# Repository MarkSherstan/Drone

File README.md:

# Drone
Mechanical, electrical, and software package for a custom quadcopter drone.

## Mechanical 
Designed using Fusion 360 and 3D printed on a Prusa MK3 printer. 

## Electrical
Custom PCBs designed in KiCad for the brain, power distribution, and signal indication. 
- Flight Controller
- Power Distribution Board 
- Lights 

## Software
C++ and custom libraries for controlling and stabilizing the UAV. Compiled with PlatformIO.

## Future Ideas
### Electrical
- Design ESCs
- 3.3 V flight controller (8 MHz suffcient?)
- Polyfuses on outputs
- PDB also ESC (active cooling?) - Have regulated outputs 
- PDB is part of frame (1 Oz copper)
- More powerful chip - RPi / STM32 / 2560 - Internet connection?

### Software 
- Test the crystal: How much time are we loosing? Try different caps.

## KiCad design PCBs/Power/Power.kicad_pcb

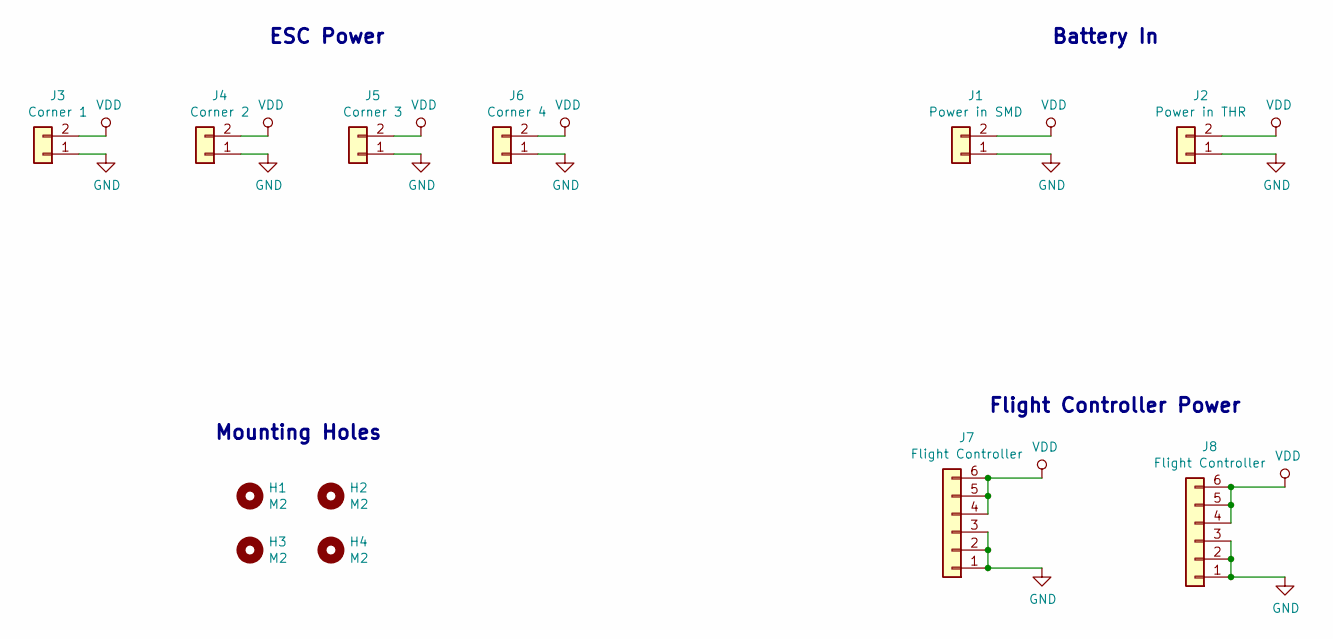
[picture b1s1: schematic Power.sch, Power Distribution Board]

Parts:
H1, H2, H3, H4: M2; MountingHole_2.2mm_M2_ISO14580_Pad
J1: Power in SMD; SMD-Power
J2: Power in THR; THR-Power
J3: Corner 1; Corner-Pad
J4: Corner 2; Corner-Pad
J5: Corner 3; Corner-Pad
J6: Corner 4; Corner-Pad
J7: Flight Controller; JST_GH_BM06B-GHS-TBT_1x06-1MP_P1.25mm_Vertical
J8: Flight Controller; JST_GH_SM06B-GHS-TB_1x06-1MP_P1.25mm_Horizontal

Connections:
GND: J1.1, J2.1, J3.1, J4.1, J5.1, J6.1, J7.1, J7.2, J7.3, J8.1, J8.2, J8.3
VDD: J1.2, J2.2, J3.2, J4.2, J5.2, J6.2, J7.4, J7.5, J7.6, J8.4, J8.5, J8.6

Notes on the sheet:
ESC Power
Battery In
Mounting Holes
Flight Controller Power

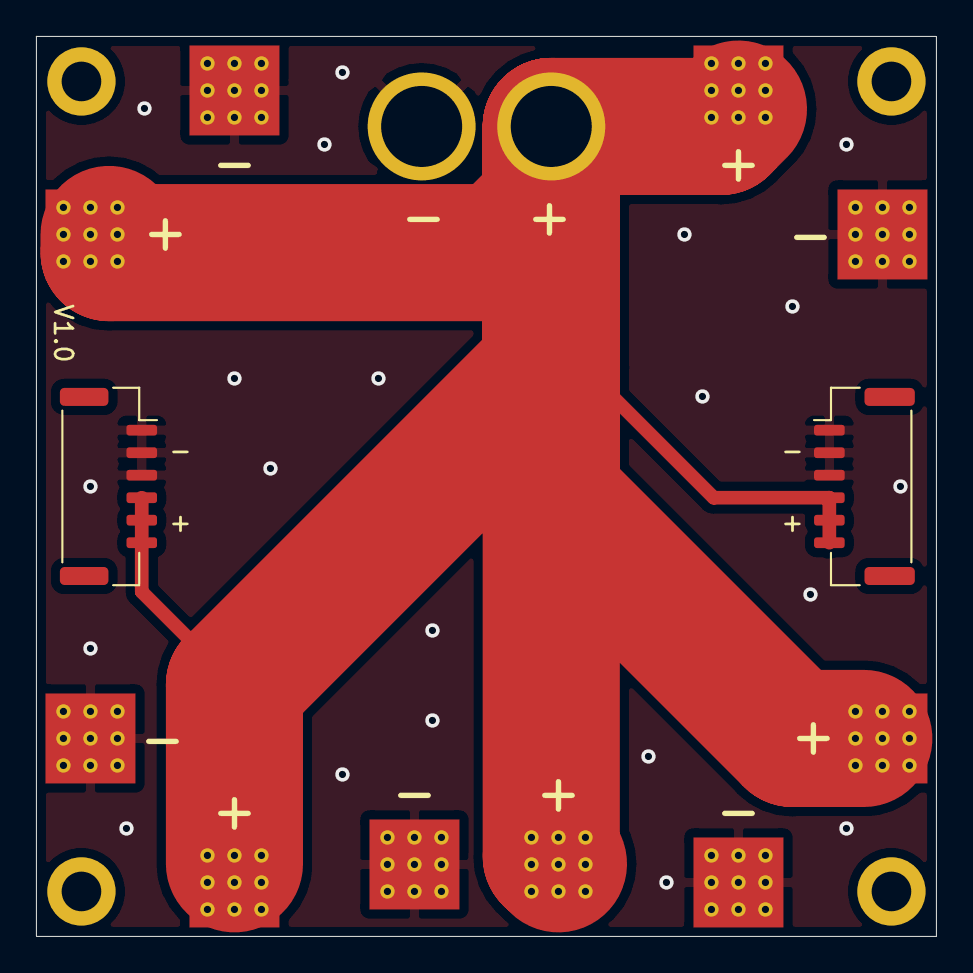
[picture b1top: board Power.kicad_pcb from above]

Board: 2 copper layers, 50.0 x 50.0 mm, 12 parts (0 on the bottom side), 2 nets.

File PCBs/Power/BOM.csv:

Reference(s),Qty,Value,LibPart,Footprint,Digi-Key #,Manufacturer,Manufacturer #
"H1, H2, H3, H4",4,M2,Mechanical:MountingHole,MountingHole:MountingHole_2.2mm_M2_ISO14580_Pad,,,
J1,1,Power in SMD,Connector_Generic:Conn_01x02,Custom:SMD-Power,,,
J2,1,Power in THR,Connector_Generic:Conn_01x02,Custom:THR-Power,,,
J3,1,Corner 1,Connector_Generic:Conn_01x02,Custom:Corner-Pad,,,
J4,1,Corner 2,Connector_Generic:Conn_01x02,Custom:Corner-Pad,,,
J5,1,Corner 3,Connector_Generic:Conn_01x02,Custom:Corner-Pad,,,
J6,1,Corner 4,Connector_Generic:Conn_01x02,Custom:Corner-Pad,,,
J7,1,Flight Controller,Connector_Generic:Conn_01x06,Connector_JST:JST_GH_BM06B-GHS-TBT_1x06-1MP_P1.25mm_Vertical,455-1582-1-ND,JST Sales America Inc.,BM06B-GHS-TBT(LF)(SN)(N)
J8,1,Flight Controller,Connector_Generic:Conn_01x06,Connector_JST:JST_GH_SM06B-GHS-TB_1x06-1MP_P1.25mm_Horizontal,455-1568-1-ND,JST Sales America Inc.,SM06B-GHS-TB(LF)(SN)

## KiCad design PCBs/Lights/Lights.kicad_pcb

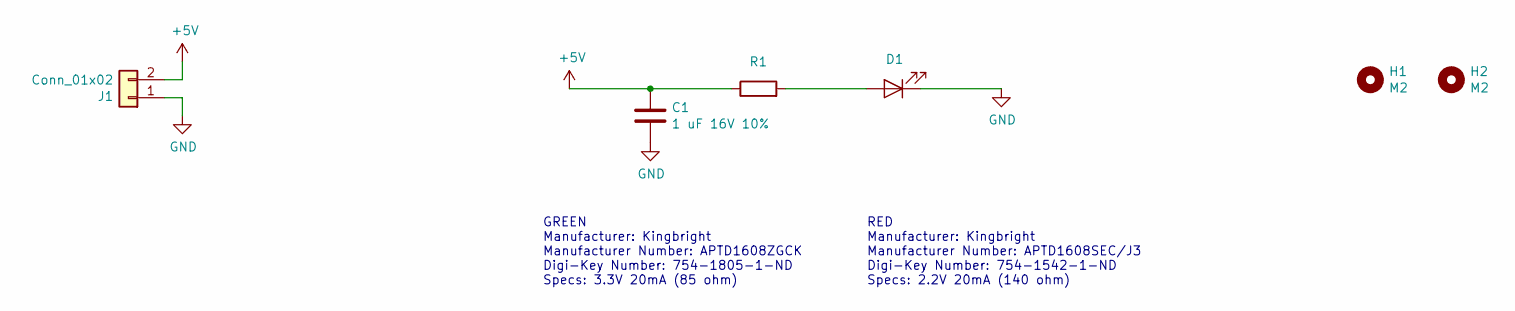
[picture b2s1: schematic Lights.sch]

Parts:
C1: 1 uF 16V 10%; C_0603_1608Metric_Pad1.05x0.95mm_HandSolder
D1: See Notes; LED_0603_1608Metric_Pad1.05x0.95mm_HandSolder
H1, H2: M2; MountingHole_2.2mm_M2_ISO14580_Pad
J1: Conn_01x02; JST_GH_BM02B-GHS-TBT_1x02-1MP_P1.25mm_Vertical; Manufacturer # BM02B-GHS-TBT(LF)(SN)(N); Digi-Key # 455-1578-1-ND
R1: See Notes; R_0603_1608Metric_Pad1.05x0.95mm_HandSolder

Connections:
+5V: C1.1, J1.2, R1.1
GND: C1.2, D1.1 (K), J1.1
unnamed: D1.2 (A), R1.2

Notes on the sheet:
GREEN Manufacturer: Kingbright Manufacturer Number: APTD1608ZGCK Digi-Key Number: 754-1805-1-ND Specs: 3.3V 20mA (85 ohm)
RED Manufacturer: Kingbright Manufacturer Number: APTD1608SEC/J3 Digi-Key Number: 754-1542-1-ND Specs: 2.2V 20mA (140 ohm)

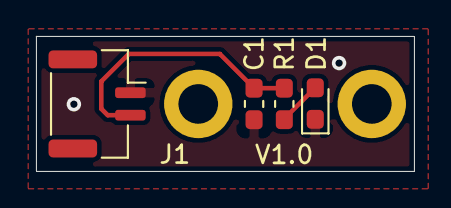
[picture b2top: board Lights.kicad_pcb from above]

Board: 2 copper layers, 21.0 x 7.5 mm, 6 parts (0 on the bottom side), 3 nets.

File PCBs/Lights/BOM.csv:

Reference(s),Qty,Value,LibPart,Footprint,Digi-Key #,"Digi-Key LinkDigi LinkDigi-Key Link",Manufacturer,Manufacturer #
C1,1,1 uF 16V 10%,Device:C,Capacitor_SMD:C_0603_1608Metric_Pad1.05x0.95mm_HandSolder,,,,
D1,1,See Notes,Device:LED,LED_SMD:LED_0603_1608Metric_Pad1.05x0.95mm_HandSolder,,,,
"H1, H2",2,M2,Mechanical:MountingHole,MountingHole:MountingHole_2.2mm_M2_ISO14580_Pad,,,,
J1,1,Conn_01x02,Connector_Generic:Conn_01x02,Connector_JST:JST_GH_SM02B-GHS-TB_1x02-1MP_P1.25mm_Horizontal,455-1564-1-ND,https://www.digikey.ca/en/products/detail/jst-sales-america-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,JST Sales America Inc.,SM02B-GHS-TB(LF)(SN)
R1,1,See Notes,Device:R,Resistor_SMD:R_0603_1608Metric_Pad1.05x0.95mm_HandSolder,,,,

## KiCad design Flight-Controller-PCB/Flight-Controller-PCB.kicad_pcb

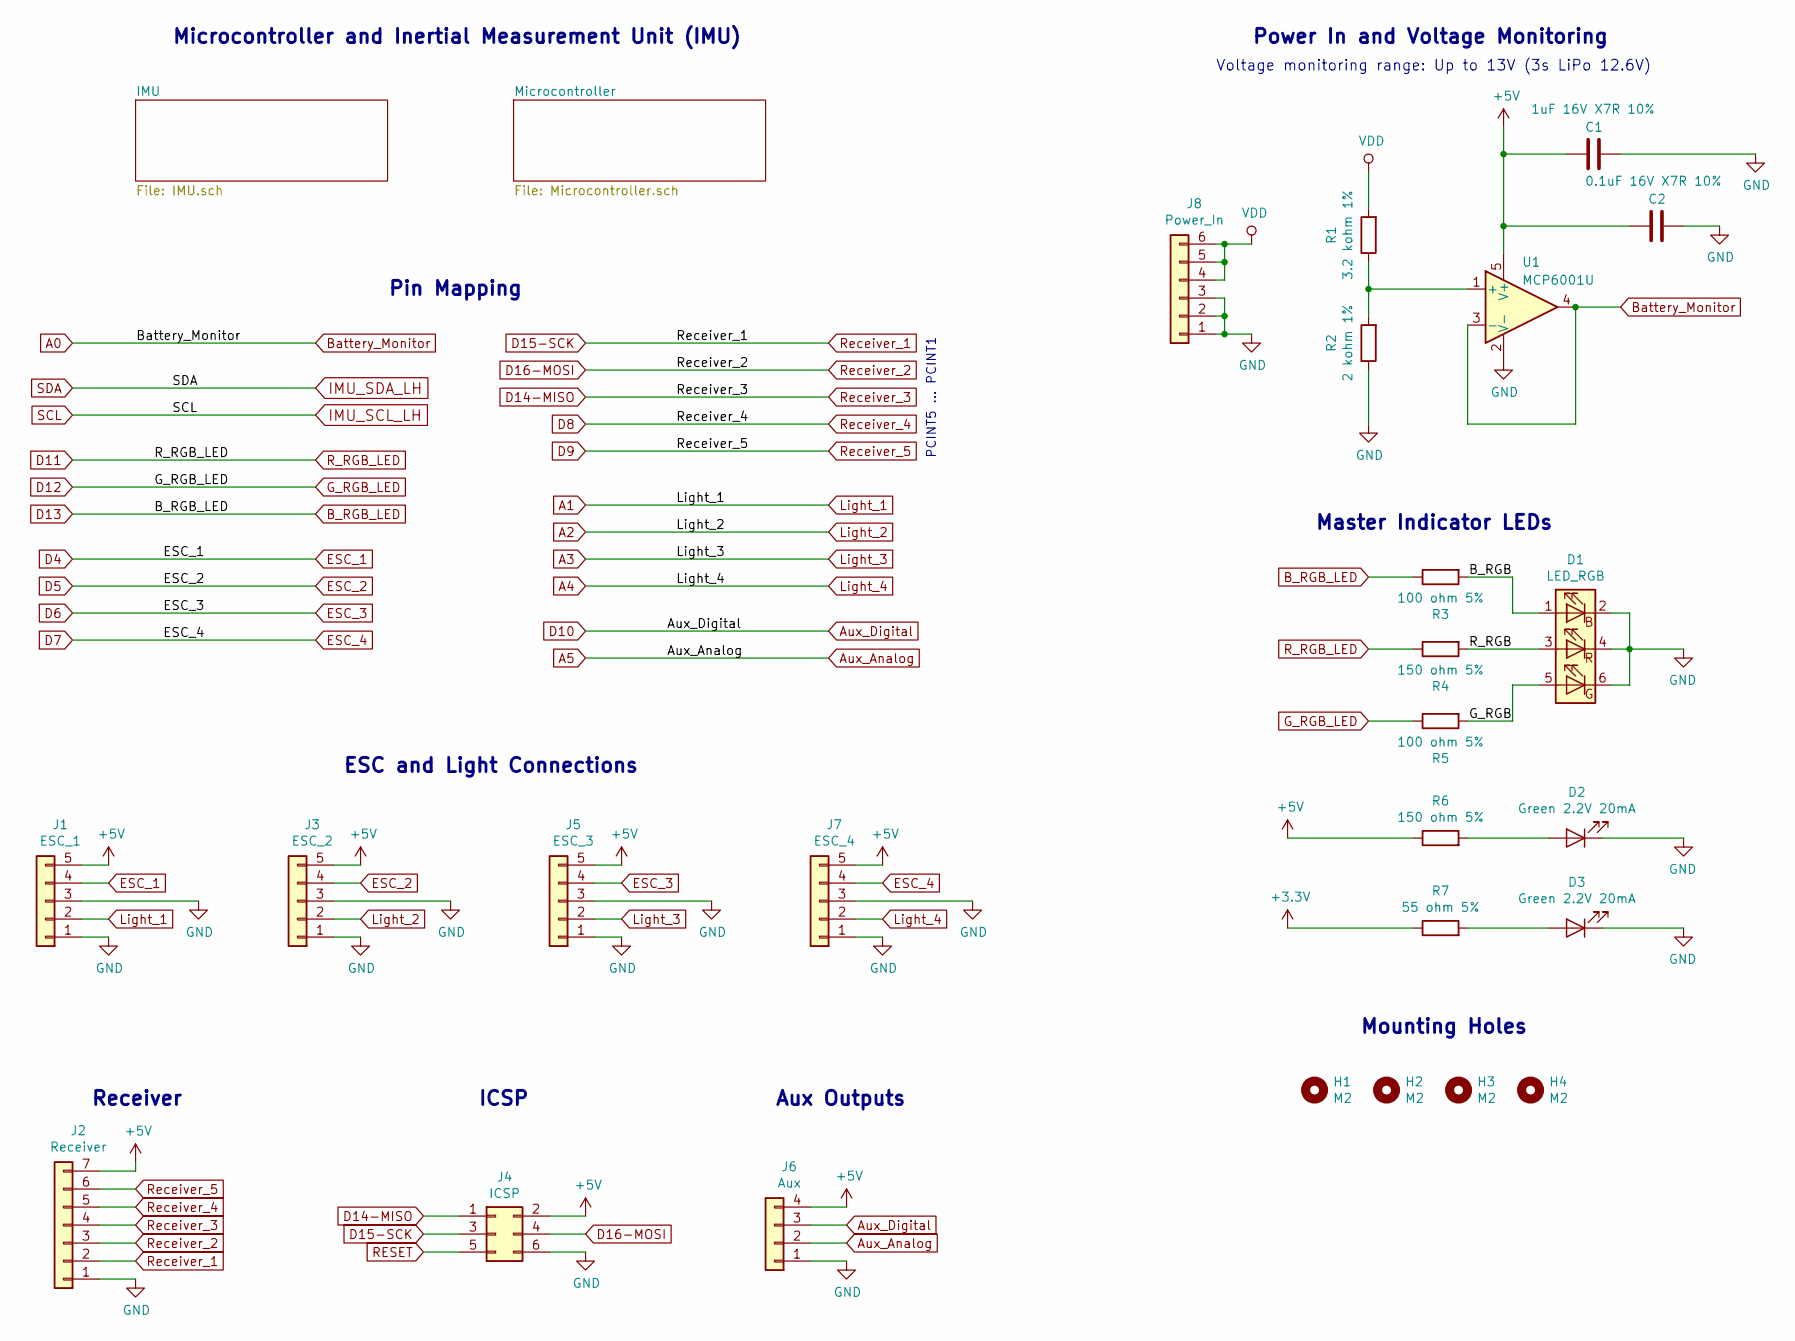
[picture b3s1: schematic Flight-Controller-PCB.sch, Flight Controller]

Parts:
C1: 1uF 16V X7R 10%; C_0603_1608Metric_Pad1.05x0.95mm_HandSolder
C2: 0.1uF 16V X7R 10%; C_0603_1608Metric_Pad1.05x0.95mm_HandSolder
D1: LED_RGB; RGB_LED; Manufacturer # EAST1616RGBA4; Digi-Key # 1080-EAST1616RGBA4CT-ND
D2, D3: Green 2.2V 20mA; LED_0603_1608Metric_Pad1.05x0.95mm_HandSolder
H1, H2, H3, H4: M2; MountingHole_2.2mm_M2_ISO7380_Pad
J1: ESC_1; JST_GH_BM05B-GHS-TBT_1x05-1MP_P1.25mm_Vertical; Manufacturer # BM05B-GHS-TBT(LF)(SN)(N); Digi-Key # 455-1581-1-ND
J2: Receiver; JST_GH_BM07B-GHS-TBT_1x07-1MP_P1.25mm_Vertical; Manufacturer # BM07B-GHS-TBT(LF)(SN)(N); Digi-Key # 455-1583-1-ND
J3: ESC_2; JST_GH_BM05B-GHS-TBT_1x05-1MP_P1.25mm_Vertical; Manufacturer # BM05B-GHS-TBT(LF)(SN)(N); Digi-Key # 455-1581-1-ND
J4: ICSP; PinHeader_2x03_P2.54mm_Vertical
J5: ESC_3; JST_GH_BM05B-GHS-TBT_1x05-1MP_P1.25mm_Vertical; Manufacturer # BM05B-GHS-TBT(LF)(SN)(N); Digi-Key # 455-1581-1-ND
J6: Aux; JST_GH_BM04B-GHS-TBT_1x04-1MP_P1.25mm_Vertical; Manufacturer # BM04B-GHS-TBT(LF)(SN)(N); Digi-Key # 455-1580-1-ND
J7: ESC_4; JST_GH_BM05B-GHS-TBT_1x05-1MP_P1.25mm_Vertical; Manufacturer # BM05B-GHS-TBT(LF)(SN)(N); Digi-Key # 455-1581-1-ND
J8: Power_In; JST_GH_BM06B-GHS-TBT_1x06-1MP_P1.25mm_Vertical; Manufacturer # BM06B-GHS-TBT(LF)(SN)(N); Digi-Key # 455-1582-1-ND
R1: 3.2 kohm 1%; R_0603_1608Metric_Pad1.05x0.95mm_HandSolder
R2: 2 kohm 1%; R_0603_1608Metric_Pad1.05x0.95mm_HandSolder
R3, R5: 100 ohm 5%; R_0603_1608Metric_Pad1.05x0.95mm_HandSolder
R4, R6: 150 ohm 5%; R_0603_1608Metric_Pad1.05x0.95mm_HandSolder
R7: 55 ohm 5%; R_0603_1608Metric_Pad1.05x0.95mm_HandSolder
U1: MCP6001U; SOT-23-5; Manufacturer # MCP6001UT-I/OT; Digi-Key # MCP6001UT-I/OTCT-ND

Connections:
+3V3: R7.1; also elsewhere on the board
+5V: C1.2, C2.2, J1.5, J2.7, J3.5, J4.2, J5.5, J6.4, J7.5, R6.1, U1.5 (V+); also elsewhere on the board
/B_RGB: D1.1 (RA), R3.2
/G_RGB: D1.5 (BA), R5.2
/R_RGB: D1.3 (GA), R4.2
A0: U1.3 (-), U1.4; also elsewhere on the board
A1: J1.2; also elsewhere on the board
A2: J3.2; also elsewhere on the board
A3: J5.2; also elsewhere on the board
A4: J7.2; also elsewhere on the board
A5: J6.2; also elsewhere on the board
Aux_Digital: J6.3; also elsewhere on the board
B_RGB_LED: R3.1; also elsewhere on the board
D4: J1.4; also elsewhere on the board
D5: J3.4; also elsewhere on the board
D6: J5.4; also elsewhere on the board
D7: J7.4; also elsewhere on the board
D8: J2.5; also elsewhere on the board
D9: J2.6; also elsewhere on the board
D11: R4.1; also elsewhere on the board
D12: R5.1; also elsewhere on the board
D14-MISO: J2.4, J4.1; also elsewhere on the board
D15-SCK: J2.2, J4.3; also elsewhere on the board
D16-MOSI: J2.3, J4.4; also elsewhere on the board
GND: C1.1, C2.1, D1.2 (RK), D1.4 (GK), D1.6 (BK), D2.1 (K), D3.1 (K), J1.1, J1.3, J2.1, J3.1, J3.3, J4.6, J5.1, J5.3, J6.1, J7.1, J7.3, J8.1, J8.2, J8.3, R2.1, U1.2 (V-); also elsewhere on the board
unnamed: D2.2 (A), R6.2
unnamed: D3.2 (A), R7.2
unnamed: R1.1, R2.2, U1.1 (+)
RESET: J4.5; also elsewhere on the board
VDD: J8.4, J8.5, J8.6, R1.2; also elsewhere on the board

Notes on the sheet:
Power In and Voltage Monitoring
Microcontroller and Inertial Measurement Unit (IMU)
Pin Mapping
ESC and Light Connections
Mounting Holes
Voltage monitoring range: Up to 13V (3s LiPo 12.6V)
Receiver
Aux Outputs
Master Indicator LEDs
ICSP
PCINT5 … PCINT1

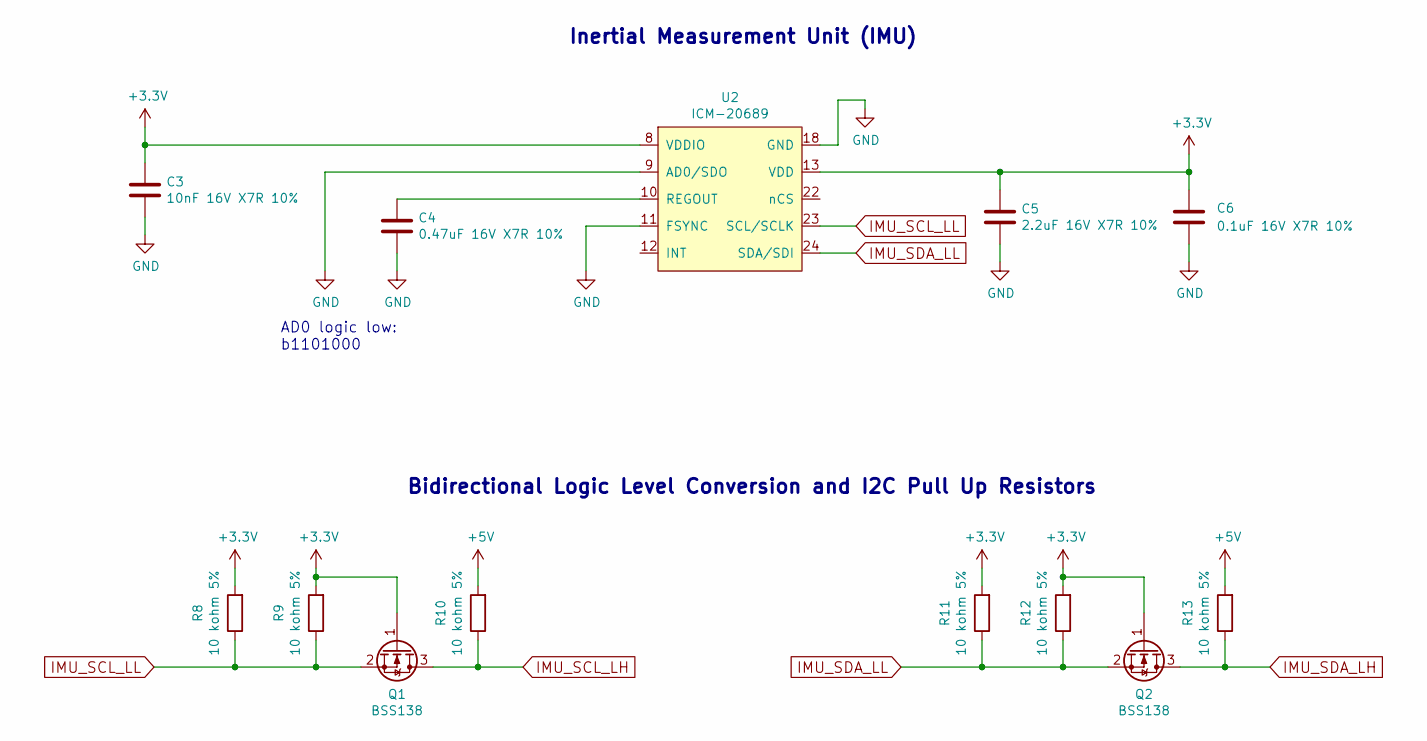
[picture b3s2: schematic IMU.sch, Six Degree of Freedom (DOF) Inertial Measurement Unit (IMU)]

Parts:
C3: 10nF 16V X7R 10%; C_0603_1608Metric_Pad1.05x0.95mm_HandSolder
C4: 0.47uF 16V X7R 10%; C_0603_1608Metric_Pad1.05x0.95mm_HandSolder
C5: 2.2uF 16V X7R 10%; C_0603_1608Metric_Pad1.05x0.95mm_HandSolder
C6: 0.1uF 16V X7R 10%; C_0603_1608Metric_Pad1.05x0.95mm_HandSolder
Q1, Q2: BSS138; SOT-23; Manufacturer # BSS138; Digi-Key # BSS138CT-ND
R8, R9, R10, R11, R12, R13: 10 kohm 5%; R_0603_1608Metric_Pad1.05x0.95mm_HandSolder
U2: ICM-20689; QFN-24-1EP_4x4mm_P0.5mm_EP2.8x2.8mm; Manufacturer # ICM-20689; Digi-Key # 1428-1059-1-ND

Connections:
+3V3: C3.1, C5.1, C6.2, Q1.1 (G), Q2.1 (G), R8.2, R9.2, R11.2, R12.2, U2.8 (VDDIO), U2.13 (VDD); also elsewhere on the board
+5V: R10.2, R13.2; also elsewhere on the board
GND: C3.2, C4.2, C5.2, C6.1, U2.9 (AD0/SDO), U2.11 (FSYNC), U2.18 (GND); also elsewhere on the board
IMU_SCL_LL: Q1.2 (S), R8.1, R9.1, U2.23 (SCL/SCLK)
IMU_SDA_LL: Q2.2 (S), R11.1, R12.1, U2.24 (SDA/SDI)
unnamed: C4.1, U2.10 (REGOUT)

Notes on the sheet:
AD0 logic low: b1101000
Inertial Measurement Unit (IMU)
Bidirectional Logic Level Conversion and I2C Pull Up Resistors

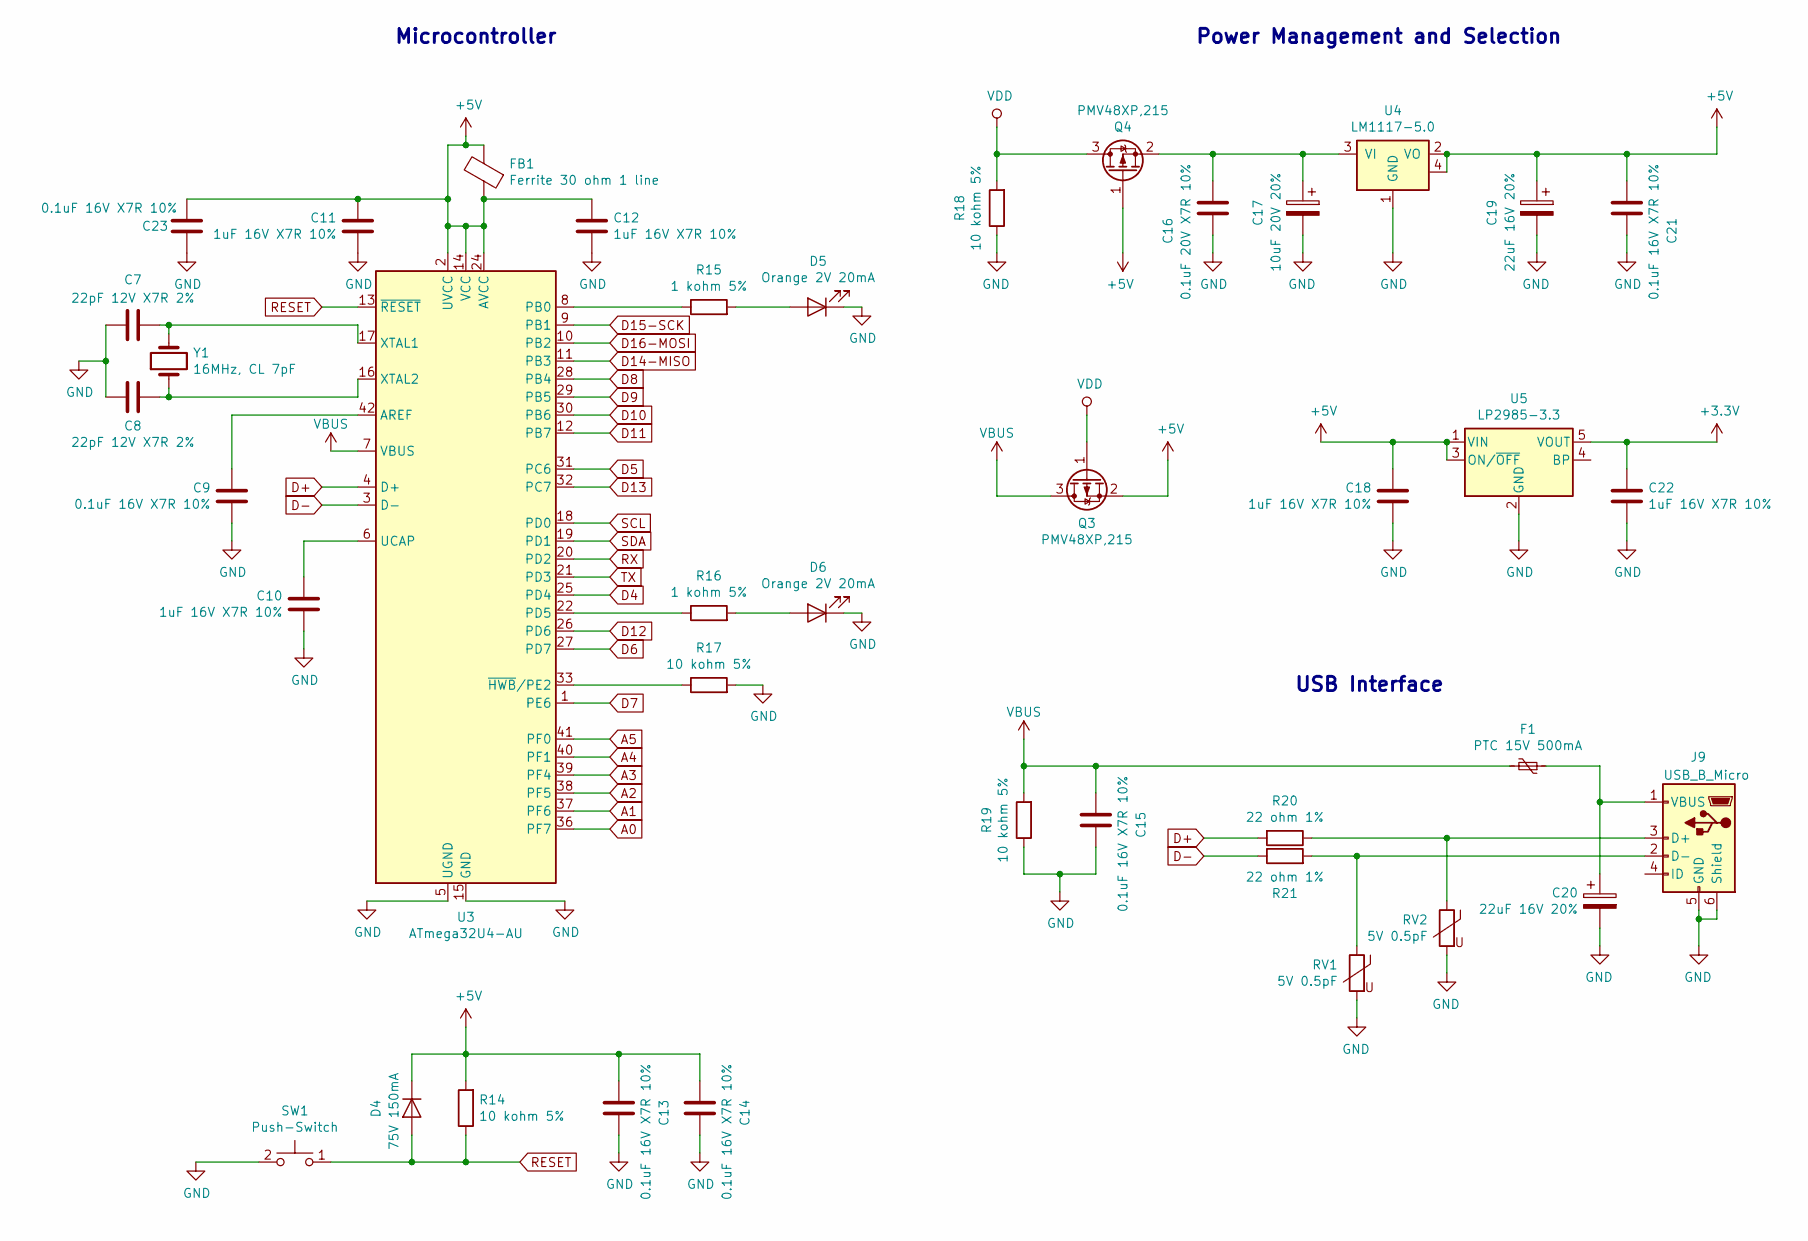
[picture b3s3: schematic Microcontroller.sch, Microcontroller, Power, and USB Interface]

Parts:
C7, C8: 22pF 12V X7R 2%; C_0603_1608Metric_Pad1.05x0.95mm_HandSolder
C9, C13, C14, C15, C21, C23: 0.1uF 16V X7R 10%; C_0603_1608Metric_Pad1.05x0.95mm_HandSolder
C10, C11, C12, C18, C22: 1uF 16V X7R 10%; C_0603_1608Metric_Pad1.05x0.95mm_HandSolder
C16: 0.1uF 20V X7R 10%; C_0603_1608Metric_Pad1.05x0.95mm_HandSolder
C17: 10uF 20V 20%; C_0603_1608Metric_Pad1.05x0.95mm_HandSolder
C19, C20: 22uF 16V 20%; C_0603_1608Metric_Pad1.05x0.95mm_HandSolder
D4: 75V 150mA; D_0603_1608Metric_Pad1.05x0.95mm_HandSolder; Manufacturer # TS4148C RZG; Digi-Key # TS4148CRZGCT-ND
D5, D6: Orange 2V 20mA; LED_0603_1608Metric_Pad1.05x0.95mm_HandSolder
F1: PTC 15V 500mA; Fuse_1206_3216Metric_Pad1.42x1.75mm_HandSolder; Manufacturer # PTS120615V050; Digi-Key # 283-3140-1-ND
FB1: Ferrite 30 ohm 1 line; R_0603_1608Metric_Pad1.05x0.95mm_HandSolder; Manufacturer # MH1608-300Y; Digi-Key # MH1608-300YCT-ND
J9: USB_B_Micro; USB_Micro-B_Molex-105017-0001; Manufacturer # 105017-0001; Digi-Key # WM1399CT-ND
Q3, Q4: PMV48XP,215; SOT-23; Manufacturer # PMV48XP,215; Digi-Key # 1727-5907-1-ND
R14, R17, R18, R19: 10 kohm 5%; R_0603_1608Metric_Pad1.05x0.95mm_HandSolder
R15, R16: 1 kohm 5%; R_0603_1608Metric_Pad1.05x0.95mm_HandSolder
R20, R21: 22 ohm 1%; R_0603_1608Metric_Pad1.05x0.95mm_HandSolder
RV1, RV2: 5V 0.5pF; R_0603_1608Metric_Pad1.05x0.95mm_HandSolder; Manufacturer # CG0603MLC-05E; Digi-Key # CG0603MLC-05ECT-ND
SW1: Push-Switch; Switch; Manufacturer # RS-187R05A2-DS MT RT; Digi-Key # CKN10361CT-ND
U3: ATmega32U4-AU; TQFP-44_10x10mm_P0.8mm; Manufacturer # ATMEGA32U4RC-AU; Digi-Key # ATMEGA32U4RC-AU-ND
U4: LM1117-5.0; SOT-223; Manufacturer # LM1117IMP-5.0/NOPB; Digi-Key # LM1117IMP-5.0/NOPBCT-ND
U5: LP2985-3.3; SOT-23-5; Manufacturer # LP2985-33DBVR; Digi-Key # 296-18476-1-ND
Y1: 16MHz, CL 7pF; Crystal; Manufacturer # ABM8W-16.0000MHZ-7-D1X-T3; Digi-Key # 535-14027-1-ND

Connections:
+3V3: C22.1, U5.5 (VOUT); also elsewhere on the board
+5V: C11.1, C12.1, C13.1, C14.1, C18.1, C19.1, C21.1, C23.1, D4.1 (K), FB1.1, FB1.2, Q3.2 (S), Q4.1 (G), R14.2, U3.2 (UVCC), U3.14 (VCC), U3.24 (AVCC), U3.34 (VCC), U3.44 (AVCC), U4.2 (VO), U4.4, U5.1 (VIN), U5.3 (ON/~OFF~); also elsewhere on the board
A0: U3.36 (PF7); also elsewhere on the board
A1: U3.37 (PF6); also elsewhere on the board
A2: U3.38 (PF5); also elsewhere on the board
A3: U3.39 (PF4); also elsewhere on the board
A4: U3.40 (PF1); also elsewhere on the board
A5: U3.41 (PF0); also elsewhere on the board
Aux_Digital: U3.30 (PB6); also elsewhere on the board
B_RGB_LED: U3.32 (PC7); also elsewhere on the board
D4: U3.25 (PD4); also elsewhere on the board
D5: U3.31 (PC6); also elsewhere on the board
D6: U3.27 (PD7); also elsewhere on the board
D7: U3.1 (PE6); also elsewhere on the board
D8: U3.28 (PB4); also elsewhere on the board
D9: U3.29 (PB5); also elsewhere on the board
D11: U3.12 (PB7); also elsewhere on the board
D12: U3.26 (PD6); also elsewhere on the board
D14-MISO: U3.11 (PB3); also elsewhere on the board
D15-SCK: U3.9 (PB1); also elsewhere on the board
D16-MOSI: U3.10 (PB2); also elsewhere on the board
D+: R20.2, U3.4 (D+)
D-: R21.1, U3.3 (D-)
GND: C7.2, C8.1, C9.2, C10.2, C11.2, C12.2, C13.2, C14.2, C15.2, C16.2, C17.2, C18.2, C19.2, C20.2, C21.2, C22.2, C23.2, D5.1 (K), D6.1 (K), J9.5 (GND), J9.6 (Shield), R17.2, R18.1, R19.1, RV1.2, RV2.2, SW1.2, U3.5 (UGND), U3.15 (GND), U3.23 (GND), U3.35 (GND), U3.43 (GND), U4.1 (GND), U5.2 (GND); also elsewhere on the board
unnamed: C7.1, U3.17 (XTAL1), Y1.2
unnamed: C8.2, U3.16 (XTAL2), Y1.1
unnamed: C9.1, U3.42 (AREF)
unnamed: C10.1, U3.6 (UCAP)
unnamed: C16.1, C17.1, Q4.2 (S), U4.3 (VI)
unnamed: C20.1, F1.1, J9.1 (VBUS)
unnamed: D5.2 (A), R15.2
unnamed: D6.2 (A), R16.2
unnamed: J9.2 (D-), R21.2, RV1.1
unnamed: J9.3 (D+), R20.1, RV2.1
unnamed: R15.1, U3.8 (PB0)
unnamed: R16.1, U3.22 (PD5)
unnamed: R17.1, U3.33 (~HWB~/PE2)
RESET: D4.2 (A), R14.1, SW1.1, U3.13 (~RESET); also elsewhere on the board
VBUS: C15.1, F1.2, Q3.3 (D), R19.2, U3.7 (VBUS)
VDD: Q3.1 (G), Q4.3 (D), R18.2; also elsewhere on the board

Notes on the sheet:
Microcontroller
USB Interface
Power Management and Selection

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
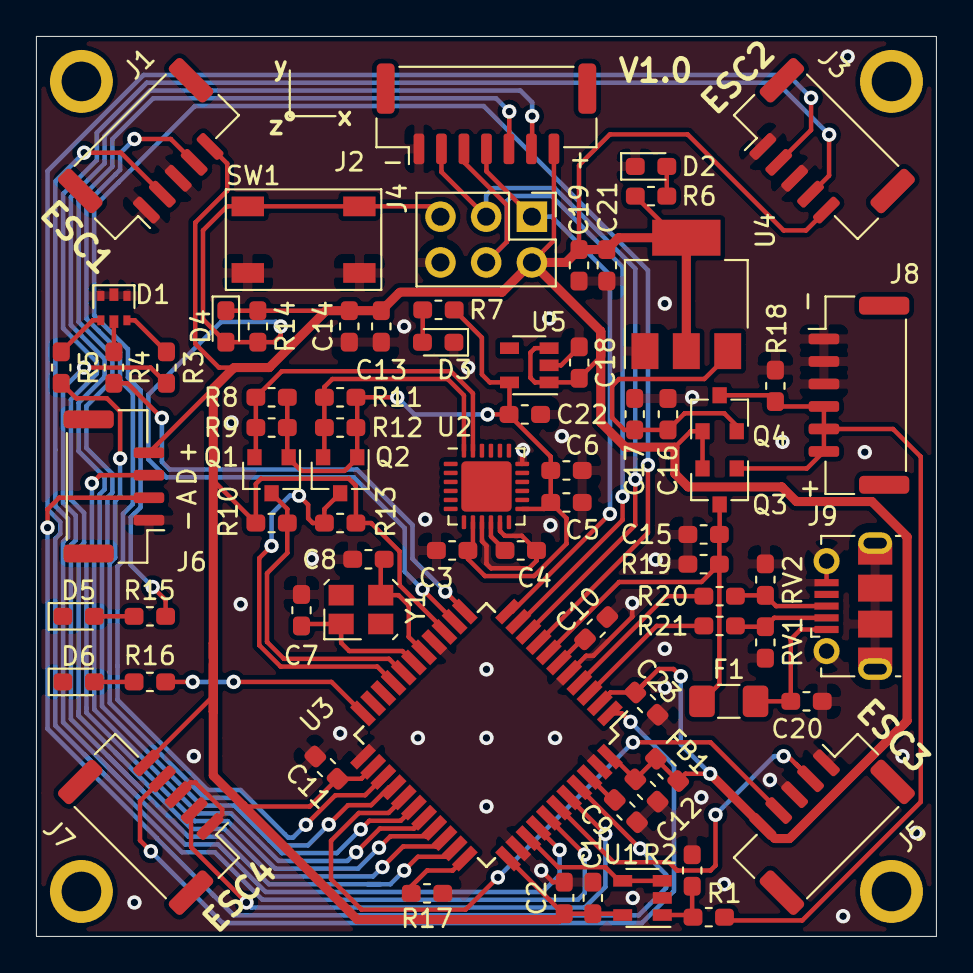
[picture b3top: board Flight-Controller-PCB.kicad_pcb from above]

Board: 2 copper layers, 50.0 x 50.0 mm, 78 parts (0 on the bottom side), 51 nets.

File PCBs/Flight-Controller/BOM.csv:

Reference(s),Qty,Value,LibPart,Footprint,Digi-Key #,Manufacturer,Manufacturer #,Digi-Key Link
"C1, C10, C11, C12, C18, C22",6,1uF 16V X7R 10%,Device:C,Capacitor_SMD:C_0603_1608Metric_Pad1.05x0.95mm_HandSolder,,,,
"C2, C6, C9, C13, C14, C15, C21",7,0.1uF 16V X7R 10%,Device:C,Capacitor_SMD:C_0603_1608Metric_Pad1.05x0.95mm_HandSolder,,,,
C3,1,10nF 16V X7R 10%,Device:C,Capacitor_SMD:C_0603_1608Metric_Pad1.05x0.95mm_HandSolder,,,,
C4,1,0.47uF 16V X7R 10%,Device:C,Capacitor_SMD:C_0603_1608Metric_Pad1.05x0.95mm_HandSolder,,,,
C5,1,2.2uF 16V X7R 10%,Device:C,Capacitor_SMD:C_0603_1608Metric_Pad1.05x0.95mm_HandSolder,,,,
"C7, C8",2,22pF 12V X7R 2%,Device:C,Capacitor_SMD:C_0603_1608Metric_Pad1.05x0.95mm_HandSolder,,,,
C16,1,0.1uF 20V X7R 10%,Device:C,Capacitor_SMD:C_0603_1608Metric_Pad1.05x0.95mm_HandSolder,,,,
C17,1,10uF 20V 20%,Device:CP,Capacitor_SMD:C_0603_1608Metric_Pad1.05x0.95mm_HandSolder,,,,
"C19, C20",2,22uF 16V 20%,Device:CP,Capacitor_SMD:C_0603_1608Metric_Pad1.05x0.95mm_HandSolder,,,,
D1,1,LED_RGB,Custom:LED_RGB,Custom:RGB_LED,1080-EAST1616RGBA4CT-ND,Everlight Electronics Co Ltd,EAST1616RGBA4,https://www.digikey.ca/en/products/detail/everlight-electron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
"D2, D3",2,Green 2.2V 20mA,Device:LED,LED_SMD:LED_0603_1608Metric_Pad1.05x0.95mm_HandSolder,,,,
D4,1,75V 150mA,Device:D,Diode_SMD:D_0603_1608Metric_Pad1.05x0.95mm_HandSolder,TS4148CRZGCT-ND,Taiwan Semiconductor Corporation,TS4148C RZG,https://www.digikey.ca/en/products/detail/taiwan-semiconduct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
"D5, D6",2,Orange 2V 20mA,Device:LED,LED_SMD:LED_0603_1608Metric_Pad1.05x0.95mm_HandSolder,,,,
F1,1,PTC 15V 500mA,Device:Polyfuse_Small,Fuse:Fuse_1206_3216Metric_Pad1.42x1.75mm_HandSolder,283-3140-1-ND,Eaton - Electronics Division,PTS120615V050,https://www.digikey.ca/en/products/detail/eaton-electronics-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
FB1,1,Ferrite 30 ohm 1 line,Device:Ferrite_Bead,Diode_SMD:D_0603_1608Metric_Pad1.05x0.95mm_HandSolder,MH1608-300YCT-ND,Bourns Inc.,MH1608-300Y,https://www.digikey.ca/en/products/detail/bourns-inc/MH1608-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
"H1, H2, H3, H4",4,M2,Mechanical:MountingHole,MountingHole:MountingHole_2.2mm_M2_ISO7380_Pad,,,,
J1,1,ESC_1,Connector_Generic:Conn_01x05,Connector_JST:JST_GH_BM05B-GHS-TBT_1x05-1MP_P1.25mm_Vertical,455-1581-1-ND,JST Sales America Inc.,BM05B-GHS-TBT(LF)(SN)(N),https://www.digikey.ca/en/products/detail/jst-sales-america-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
J2,1,Receiver,Connector_Generic:Conn_01x07,Connector_JST:JST_GH_BM07B-GHS-TBT_1x07-1MP_P1.25mm_Vertical,455-1583-1-ND,JST Sales America Inc.,BM07B-GHS-TBT(LF)(SN)(N),https://www.digikey.ca/en/products/detail/jst-sales-america-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
J3,1,ESC_2,Connector_Generic:Conn_01x05,Connector_JST:JST_GH_BM05B-GHS-TBT_1x05-1MP_P1.25mm_Vertical,455-1581-1-ND,JST Sales America Inc.,BM05B-GHS-TBT(LF)(SN)(N),https://www.digikey.ca/en/products/detail/jst-sales-america-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
J4,1,ICSP,Connector_Generic:Conn_02x03_Odd_Even,Connector_PinHeader_2.54mm:PinHeader_2x03_P2.54mm_Vertical,,,,
J5,1,ESC_3,Connector_Generic:Conn_01x05,Connector_JST:JST_GH_BM05B-GHS-TBT_1x05-1MP_P1.25mm_Vertical,455-1581-1-ND,JST Sales America Inc.,BM05B-GHS-TBT(LF)(SN)(N),https://www.digikey.ca/en/products/detail/jst-sales-america-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
J6,1,Aux,Connector_Generic:Conn_01x04,Connector_JST:JST_GH_BM04B-GHS-TBT_1x04-1MP_P1.25mm_Vertical,455-1580-1-ND,JST Sales America Inc.,BM04B-GHS-TBT(LF)(SN)(N),https://www.digikey.ca/en/products/detail/jst-sales-america-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
J7,1,ESC_4,Connector_Generic:Conn_01x05,Connector_JST:JST_GH_BM05B-GHS-TBT_1x05-1MP_P1.25mm_Vertical,455-1581-1-ND,JST Sales America Inc.,BM05B-GHS-TBT(LF)(SN)(N),https://www.digikey.ca/en/products/detail/jst-sales-america-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
J8,1,Power_In,Connector_Generic:Conn_01x06,Connector_JST:JST_GH_BM06B-GHS-TBT_1x06-1MP_P1.25mm_Vertical,455-1582-1-ND,JST Sales America Inc.,BM06B-GHS-TBT(LF)(SN)(N),https://www.digikey.ca/en/products/detail/jst-sales-america-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
J9,1,USB_B_Micro,Connector:USB_B_Micro,Connector_USB:USB_Micro-B_Molex-105017-0001,WM1399CT-ND,Molex,105017-0001,https://www.digikey.ca/en/products/detail/molex/1050170001/2350832
"Q1, Q2",2,BSS138,Transistor_FET:BSS138,Package_TO_SOT_SMD:SOT-23,BSS138CT-ND,ON Semiconductor,BSS138,https://www.digikey.ca/en/products/detail/on-semiconductor/B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
"Q3, Q4",2,"PMV48XP,215",Device:Q_PMOS_GSD,Package_TO_SOT_SMD:SOT-23,1727-5907-1-ND,Nexperia USA Inc.,"PMV48XP,215",https://www.digikey.ca/en/products/detail/nexperia-usa-inc/P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
R1,1,3.2 kohm 1%,Device:R,Resistor_SMD:R_0603_1608Metric_Pad1.05x0.95mm_HandSolder,,,,
R2,1,2 kohm 1%,Device:R,Resistor_SMD:R_0603_1608Metric_Pad1.05x0.95mm_HandSolder,,,,
"R3, R5",2,100 ohm 5%,Device:R,Resistor_SMD:R_0603_1608Metric_Pad1.05x0.95mm_HandSolder,,,,
"R4, R6",2,150 ohm 5%,Device:R,Resistor_SMD:R_0603_1608Metric_Pad1.05x0.95mm_HandSolder,,,,
R7,1,55 ohm 5%,Device:R,Resistor_SMD:R_0603_1608Metric_Pad1.05x0.95mm_HandSolder,,,,
"R8, R9, R10, R11, R12, R13, R14, R17, R18, R19",10,10 kohm 5%,Device:R,Resistor_SMD:R_0603_1608Metric_Pad1.05x0.95mm_HandSolder,,,,
"R15, R16",2,1 kohm 5%,Device:R,Resistor_SMD:R_0603_1608Metric_Pad1.05x0.95mm_HandSolder,,,,
"R20, R21",2,22 ohm 1%,Device:R,Resistor_SMD:R_0603_1608Metric_Pad1.05x0.95mm_HandSolder,,,,
"RV1, RV2",2,5V 0.5pF,Device:Varistor,Diode_SMD:D_0603_1608Metric_Pad1.05x0.95mm_HandSolder,CG0603MLC-05ECT-ND,Bourns Inc.,CG0603MLC-05E,https://www.digikey.ca/en/products/detail/bourns-inc/CG0603M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
SW1,1,Push-Switch,Custom:Push-Switch,Custom:Switch,CKN10361CT-ND,C&K,RS-187R05A2-DS MT RT,https://www.digikey.ca/en/products/detail/c-k/RS-187R05A2-DS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
U1,1,MCP6001U,Amplifier_Operational:MCP6001U,Package_TO_SOT_SMD:SOT-23-5,MCP6001UT-I/OTCT-ND,Microchip Technology,MCP6001UT-I/OT,https://www.digikey.ca/en/products/detail/microchip-technolo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
U2,1,ICM-20689,Custom:ICM-20689,Package_DFN_QFN:QFN-24-1EP_4x4mm_P0.5mm_EP2.8x2.8mm,1428-1059-1-ND,TDK InvenSense,ICM-20689,https://www.digikey.ca/en/products/detail/tdk-invensense/ICM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
U3,1,ATmega32U4-AU,MCU_Microchip_ATmega:ATmega32U4-AU,Package_QFP:TQFP-44_10x10mm_P0.8mm,ATMEGA32U4RC-AU-ND,Microchip Technology,ATMEGA32U4RC-AU,https://www.digikey.ca/en/products/detail/microchip-technolo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
U4,1,LM1117-5.0,Custom:LM1117-5.0,Package_TO_SOT_SMD:SOT-223,LM1117IMP-5.0/NOPBCT-ND,Texas Instruments,LM1117IMP-5.0/NOPB,https://www.digikey.ca/en/products/detail/texas-instruments/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
U5,1,LP2985-3.3,Regulator_Linear:LP2985-3.3,Package_TO_SOT_SMD:SOT-23-5,296-18476-1-ND,Texas Instruments,LP2985-33DBVR,https://www.digikey.ca/en/products/detail/texas-instruments/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
Y1,1,"16MHz, CL 7pF",Device:Crystal,Custom:Crystal,535-14027-1-ND,Abracon LLC,ABM8W-16.0000MHZ-7-D1X-T3,https://www.digikey.ca/en/products/detail/abracon-llc/ABM8W-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
